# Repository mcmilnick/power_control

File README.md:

# power_control_files
This is an iterative open source product design. It started as a way to control a coffee pot and
is evolving into a way to control anything. Accordingly, there are files for the starting proto,
proto 3D files to fit a Pi, etc. It evolves to have a custom board spin with schematic, layout,
and proper container. This will contain all firmware and phone apps as well.

For a full tutorial, visit my webpage...
https://techtures.wordpress.com/about/

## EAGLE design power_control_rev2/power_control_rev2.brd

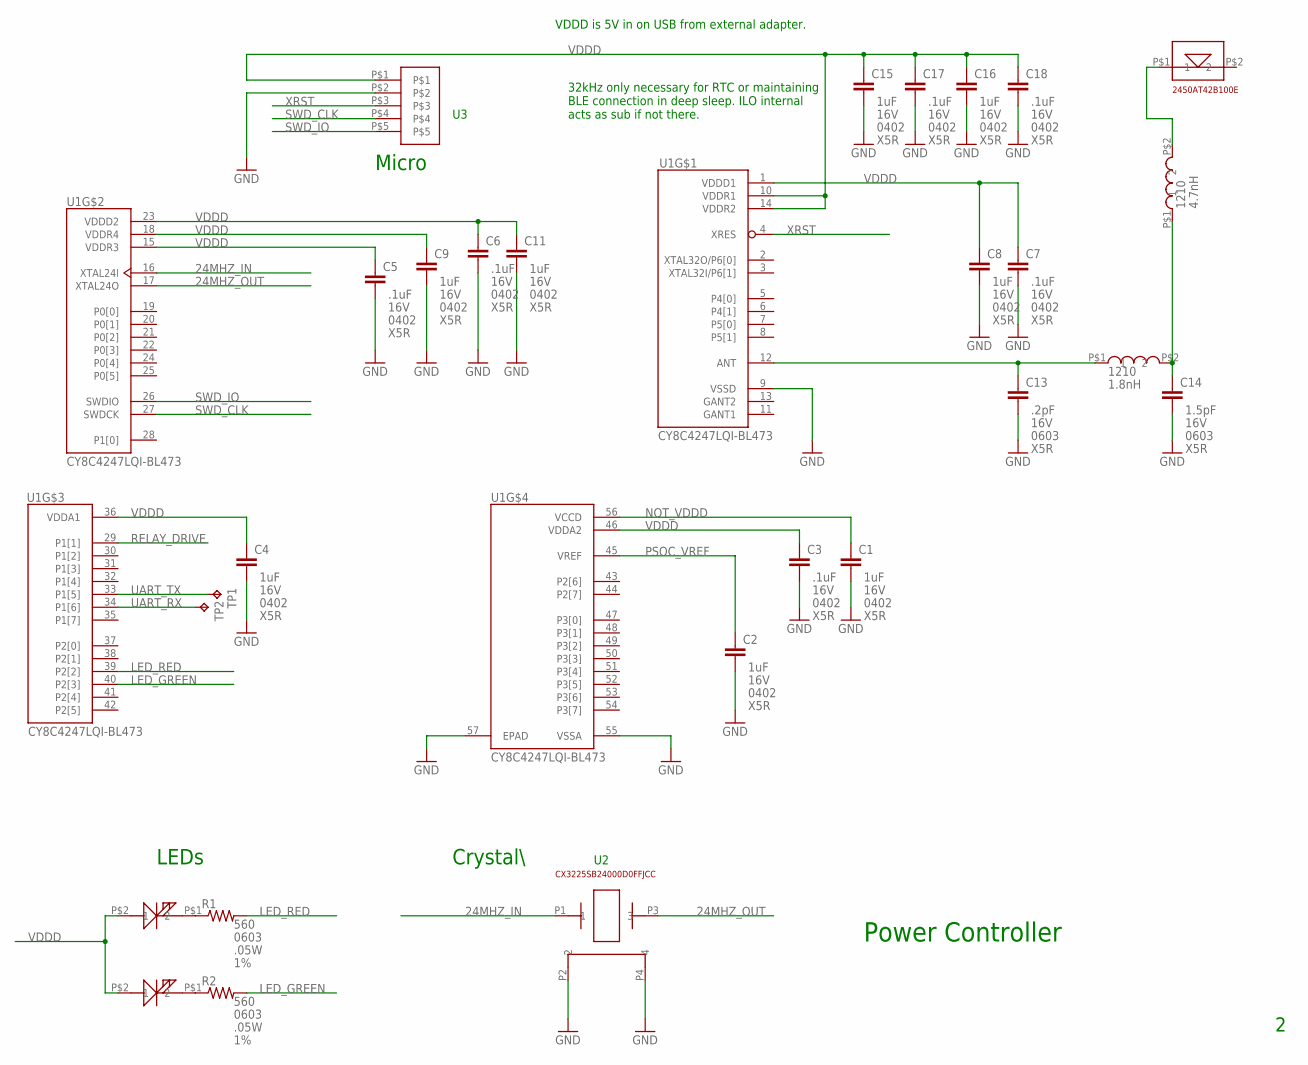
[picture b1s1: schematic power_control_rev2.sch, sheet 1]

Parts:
C1, C2, C3, C4, C5, C6, C7, C8, C9, C11, C15, C16, C17, C18: CC0402; C0402; RATING X5R; TOLERANCE 16V
C13, C14: CC0603; C0603
R1, R2: R-US_R0603; R0603; TOLERANCE 1%
TP1, TP2: TPB1,27; B1,27
U1: CY8C4247LQI-BL473; JEDEC_MO-248_QFN-56-7MMX7MM
U$1, U$8: 1210_INDUCTOR
U$2: CX3225SB24000D0FFJCC
U$3: SAMTEC1X5; 5XHEADER
U$4: 2450AT42B100E
U$5, U$6: SML-P11UTT86

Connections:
24MHZ_IN: U1.16 (XTAL24I), U$2.P1 (1)
24MHZ_OUT: U1.17 (XTAL24O), U$2.P3 (3)
GANT1: U1.11 (GANT1)
GANT2: U1.13 (GANT2)
GND: C1.2, C2.2, C3.2, C4.2, C5.2, C6.2, C7.2, C8.2, C9.2, C11.2, C13.2, C14.2, C15.2, C16.2, C17.2, C18.2, U1.9 (VSSD), U1.55 (VSSA), U1.57 (EPAD), U$2.P2 (2), U$2.P4 (4), U$3.P$2; also elsewhere on the board
LED_GREEN: R2.2, U1.40 (P2[3])
LED_RED: R1.2, U1.39 (P2[2])
unnamed: R2.1, U$6.P$1 (2)
unnamed: R1.1, U$5.P$1 (2)
unnamed: U$4.P$1 (1), U$8.P$2 (2)
unnamed: C13.1, U1.12 (ANT), U$1.P$1 (1)
unnamed: C14.1, U$1.P$2 (2), U$8.P$1 (1)
NOT_VDDD: C1.1, U1.56 (VCCD)
PSOC_VREF: C2.1, U1.45 (VREF)
RELAY_DRIVE: U1.29 (P1[1]); also elsewhere on the board
SWD_CLK: U1.27 (SWDCK), U$3.P$4
SWD_IO: U1.26 (SWDIO), U$3.P$5
UART_RX: TP2.TP, U1.34 (P1[6])
UART_TX: TP1.TP, U1.33 (P1[5])
VDDD: C3.1, C4.1, C5.1, C6.1, C7.1, C8.1, C9.1, C11.1, C15.1, C16.1, C17.1, C18.1, U1.1 (VDDD1), U1.10 (VDDR1), U1.14 (VDDR2), U1.15 (VDDR3), U1.18 (VDDR4), U1.23 (VDDD2), U1.36 (VDDA1), U1.46 (VDDA2), U$3.P$1, U$5.P$2 (1), U$6.P$2 (1); also elsewhere on the board
XRST: U1.4 (XRES), U$3.P$3

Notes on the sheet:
LEDs
Power Controller
Micro
32kHz only necessary for RTC or maintaining BLE connection in deep sleep. ILO internal acts as sub if not there.
Crystal\
VDDD is 5V in on USB from external adapter.

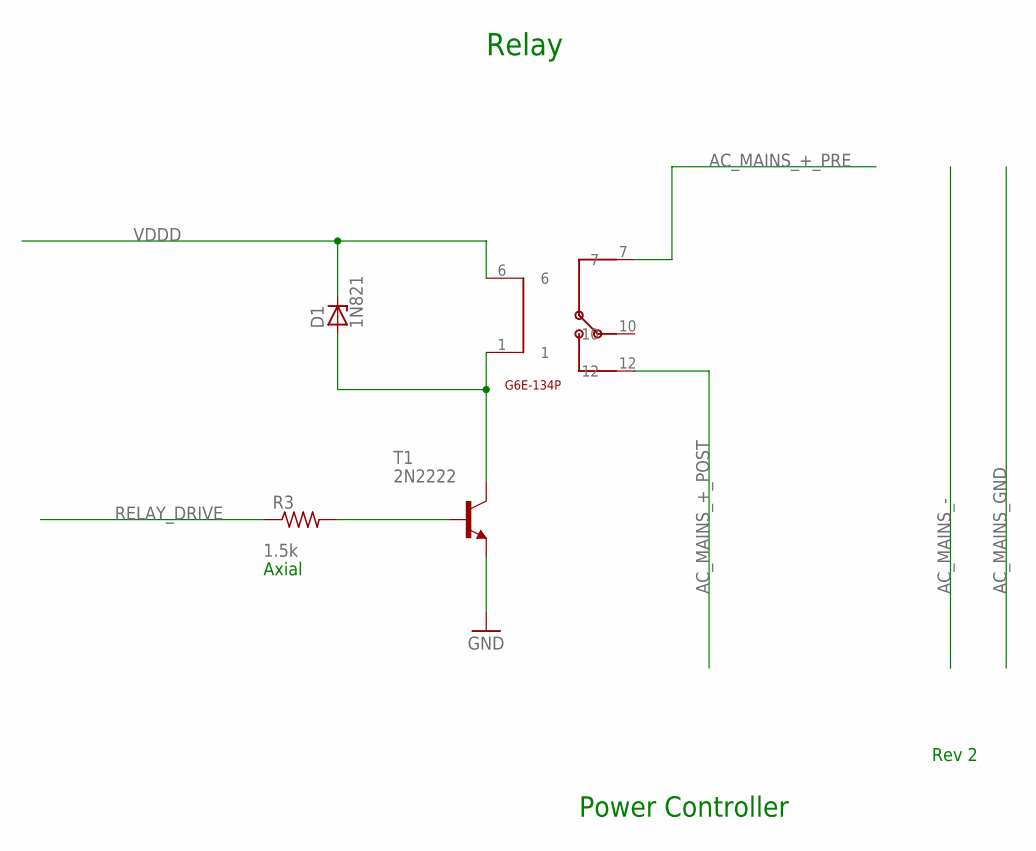
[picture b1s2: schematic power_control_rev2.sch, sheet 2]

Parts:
D1: 1N821; DO35Z10
R3: R-US_0204/2V; 0204V
T1: 2N2222; TO18
U$7: G6E-134P

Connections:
AC_MAINS_+_POST: U$7.12
AC_MAINS_+_PRE: U$7.7
GND: T1.1 (E); also elsewhere on the board
unnamed: D1.A, T1.3 (C), U$7.1
unnamed: R3.2, T1.2 (B)
RELAY_DRIVE: R3.1; also elsewhere on the board
VDDD: D1.C, U$7.6; also elsewhere on the board

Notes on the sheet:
Relay
Power Controller
Rev 2
Axial

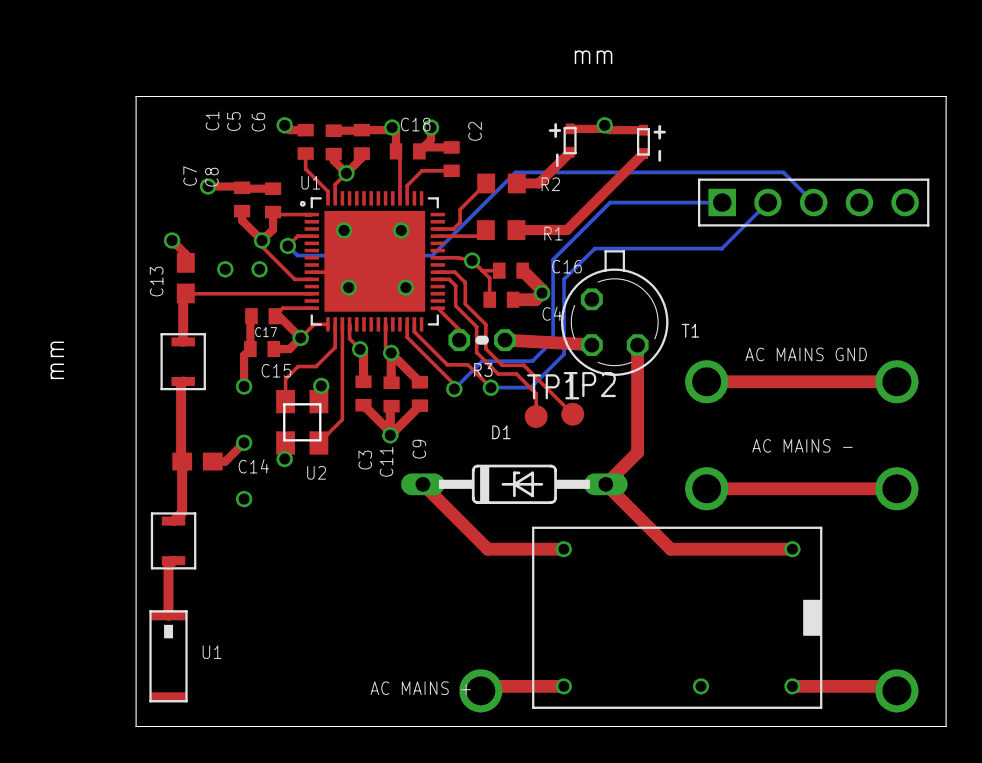
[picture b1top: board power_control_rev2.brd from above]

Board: 4 copper layers, 45.0 x 35.0 mm, 32 parts (0 on the bottom side), 21 nets.

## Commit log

2016-02-23 :neckbeard: Added .gitattributes & .gitignore files
2016-02-23 Contains first and second rev of schematic, first run PCB, BOM, mechanical files for 3D printing and laser cutting, FW, and Android APP
2016-02-24 Changed UUIDs in Android App
2016-03-08 Changed layout in rev2
    Changed pad sizes and added test points for UART.
